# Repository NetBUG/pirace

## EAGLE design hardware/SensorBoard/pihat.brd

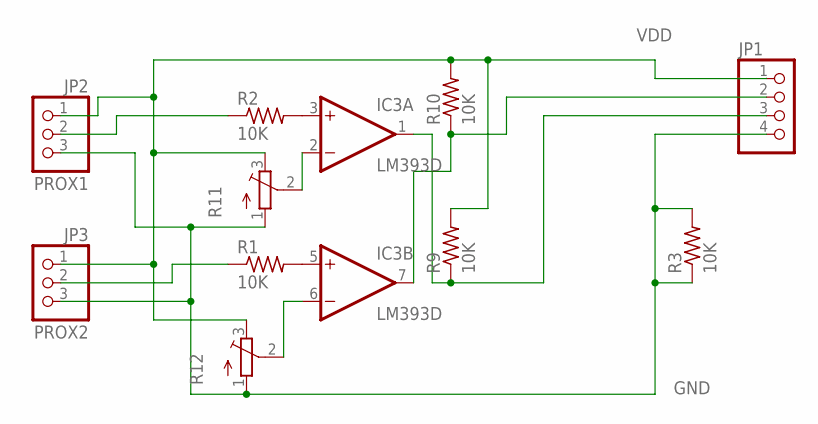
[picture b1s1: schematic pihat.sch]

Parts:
IC3: LM393D; SO08
JP1: PINHD-1X4; 1X04
JP2: PROX1; 1X03
JP3: PROX2; 1X03
R1, R2, R3, R9, R10: 10K; R1206FAB
R11, R12: TRIM_EU-3223G; 3223G

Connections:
GND: IC3.4 (V-), JP1.4, JP2.3, JP3.3, R3.1, R3.2, R11.1 (A), R12.1 (A)
unnamed: IC3.5 (+IN), R1.2
unnamed: IC3.3 (+IN), R2.2
unnamed: JP2.2, R2.1
unnamed: IC3.7 (OUT), JP1.2, R10.1
unnamed: IC3.1 (OUT), JP1.3, R9.1
unnamed: IC3.6 (-IN), R12.2 (S)
unnamed: IC3.2 (-IN), R11.2 (S)
unnamed: JP3.2, R1.1
VDD: IC3.8 (V+), JP1.1, JP2.1, JP3.1, R9.2, R10.2, R11.3 (E), R12.3 (E)

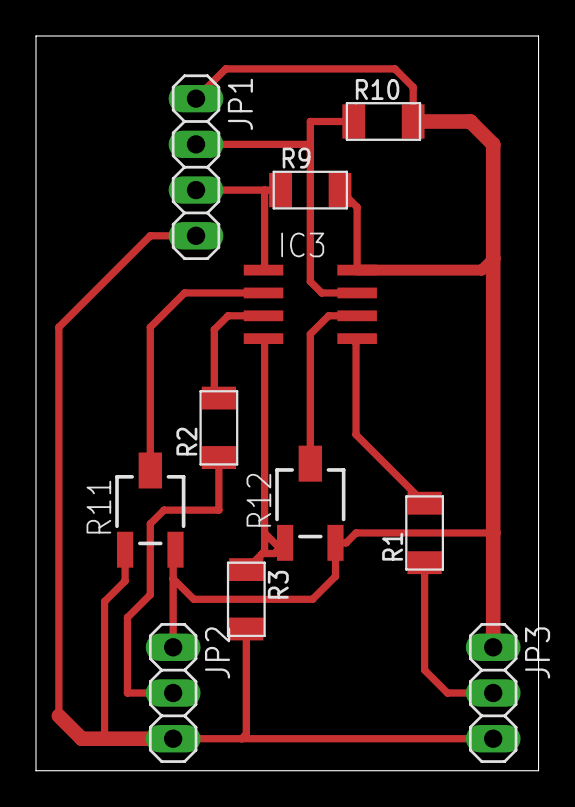
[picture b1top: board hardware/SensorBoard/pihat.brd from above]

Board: 2 copper layers, 27.9 x 40.8 mm, 11 parts (0 on the bottom side), 10 nets.

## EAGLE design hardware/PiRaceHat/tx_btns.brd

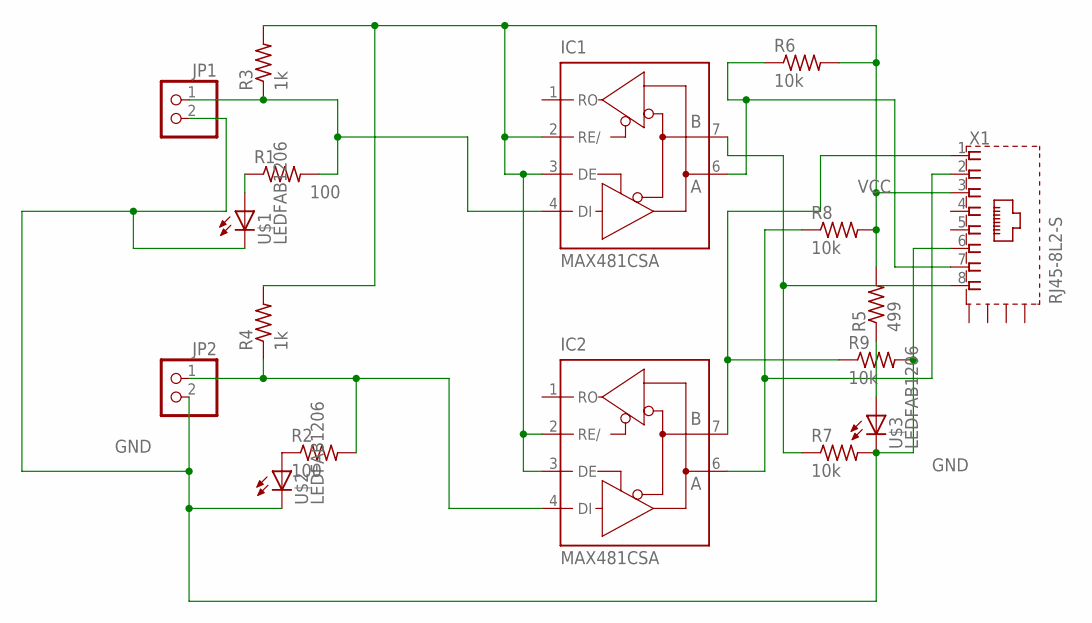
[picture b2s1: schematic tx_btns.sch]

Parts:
IC1, IC2: MAX481CSA; SO08
JP1, JP2: PINHD-1X2/90; 1X02/90
R1, R2: 100; R1206FAB
R3, R4: 1k; R1206FAB
R5: 499; R1206FAB
R6, R7, R8, R9: 10k; R1206FAB
U$1, U$2, U$3: LEDFAB1206; LED1206FAB
X1: RJ45-8L2-S; RJ45-SHIELD2

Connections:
GND: IC1.5 (GND), IC2.5 (GND), JP1.2, JP2.2, R7.2, R9.2, U$1.2 (C), U$2.2 (C), U$3.2 (C), X1.6
unnamed: R1.1, U$1.1 (A)
unnamed: R2.1, U$2.1 (A)
unnamed: R5.1, U$3.1 (A)
unnamed: IC1.4 (DI), JP1.1, R1.2, R3.1
unnamed: IC1.7 (B), R7.1, X1.8
unnamed: IC2.6 (A), R8.1, X1.2
unnamed: IC1.6 (A), R6.1, X1.7
unnamed: IC2.7 (B), R9.1, X1.1
unnamed: IC2.4 (DI), JP2.1, R2.2, R4.1
VCC: IC1.2 (RE/), IC1.3 (DE), IC1.8 (VCC), IC2.2 (RE/), IC2.3 (DE), IC2.8 (VCC), R3.2, R4.2, R5.2, R6.2, R8.2, X1.3

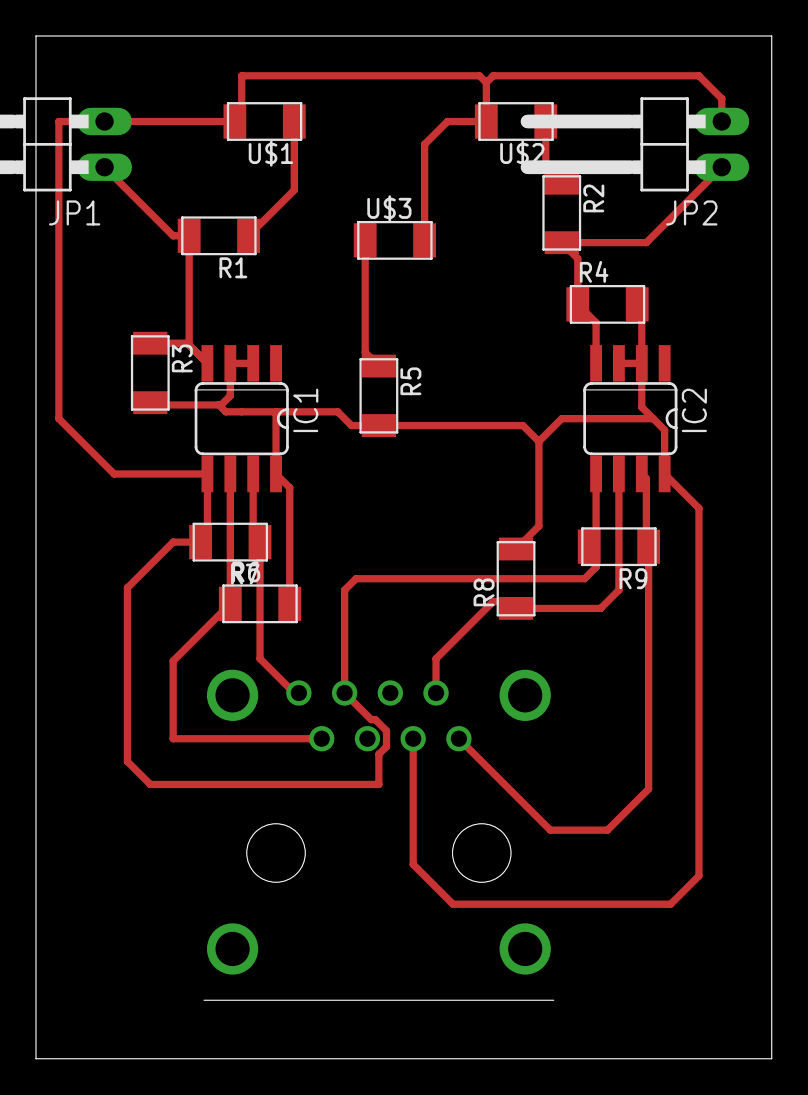
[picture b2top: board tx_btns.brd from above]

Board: 2 copper layers, 40.9 x 56.8 mm, 17 parts (1 on the bottom side), 11 nets.

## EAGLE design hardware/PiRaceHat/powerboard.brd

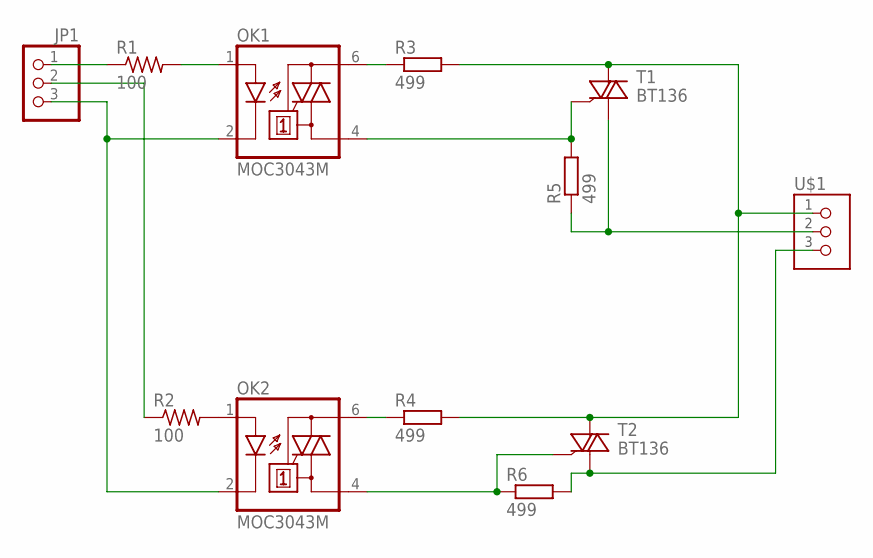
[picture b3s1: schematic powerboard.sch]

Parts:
JP1: PINHD-1X3/90; 1X03/90
OK1, OK2: MOC3043M; DIL06
R1, R2: 100; R1206FAB
R3, R4, R5, R6: 499; 0207/12
T1, T2: BT136; TO220AB
U$1: TERM-1X03'-FABLAB'; ED555DS-3DS

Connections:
unnamed: JP1.3, OK1.2 (C), OK2.2 (C)
unnamed: OK2.1 (A), R2.2
unnamed: JP1.2, R2.1
unnamed: OK1.1 (A), R1.2
unnamed: JP1.1, R1.1
unnamed: OK2.6 (A2), R4.1
unnamed: OK1.6 (A2), R3.1
unnamed: R3.2, R4.2, T1.2 (A2), T2.2 (A2), U$1.1
unnamed: R5.1, T1.1 (A1), U$1.2
unnamed: R6.2, T2.1 (A1), U$1.3
unnamed: OK1.4 (A1), R5.2, T1.3 (G)
unnamed: OK2.4 (A1), R6.1, T2.3 (G)

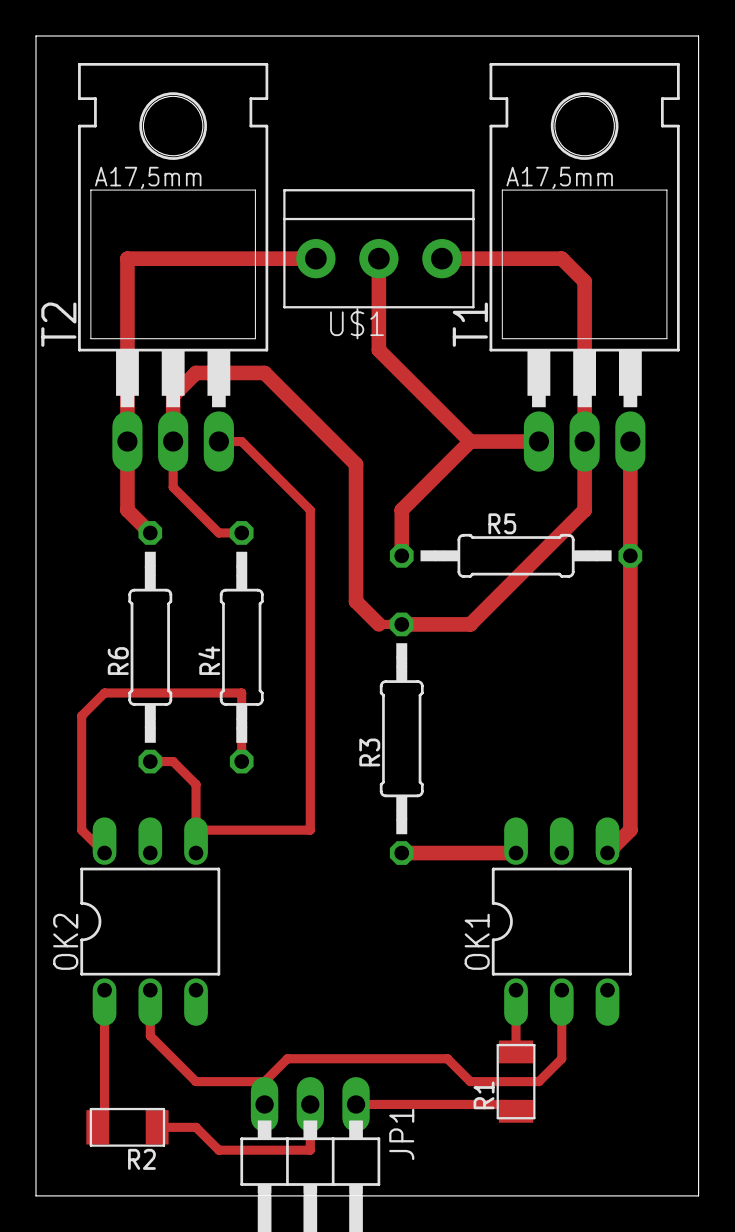
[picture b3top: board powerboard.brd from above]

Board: 2 copper layers, 36.8 x 64.4 mm, 12 parts (0 on the bottom side), 12 nets.

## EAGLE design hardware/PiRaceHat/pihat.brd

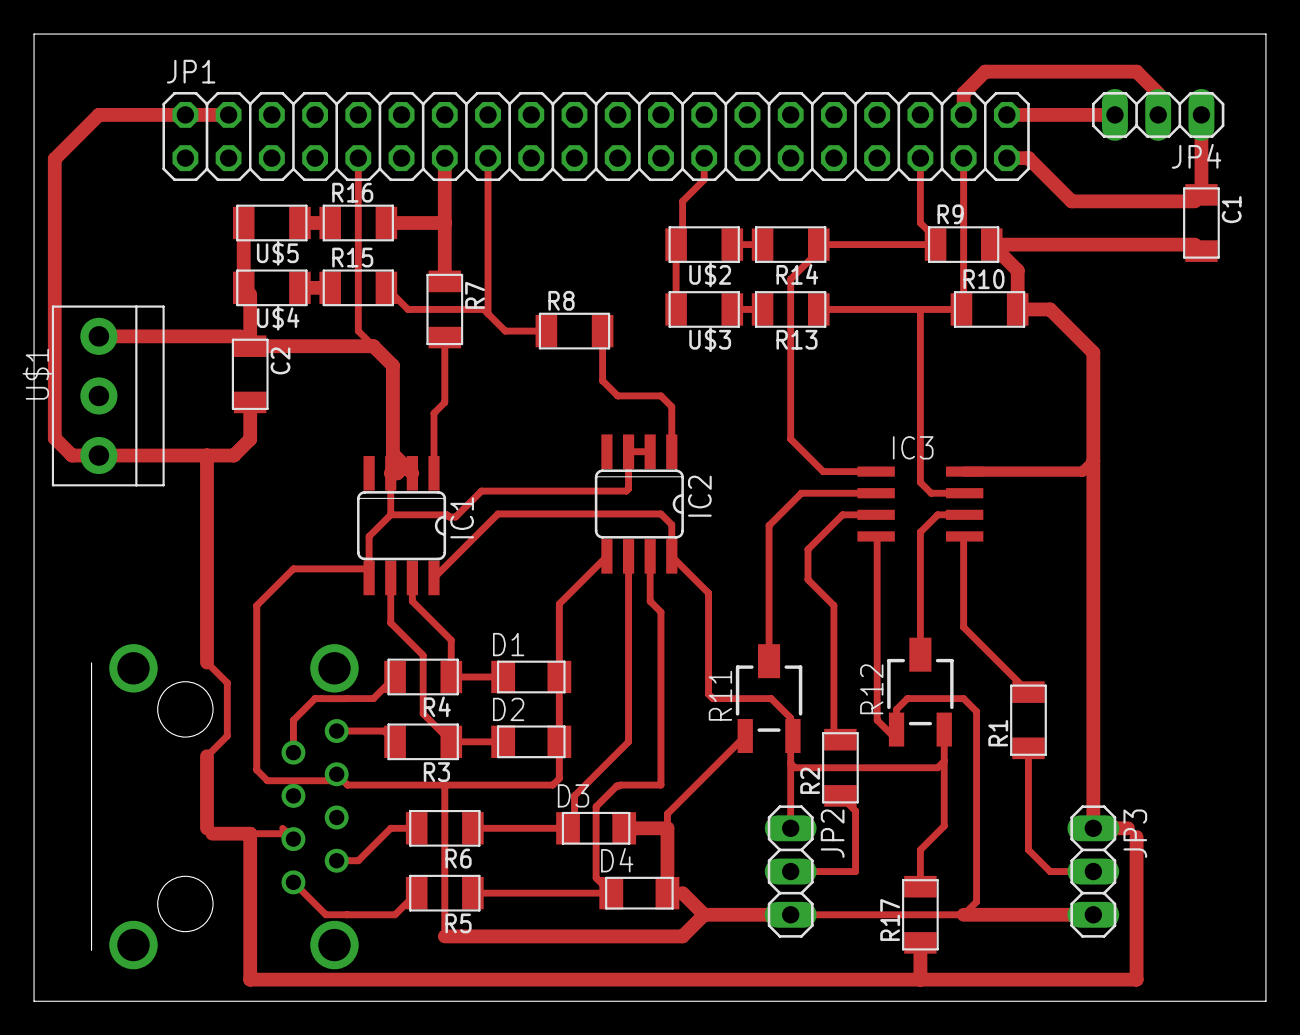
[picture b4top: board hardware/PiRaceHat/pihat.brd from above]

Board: 2 copper layers, 72.4 x 56.8 mm, 36 parts (1 on the bottom side), 28 nets.

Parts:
C1, C2: C1206FAB
D1, D2, D3, D4: CDBM1100-G; MINI-SMA
IC1, IC2: MAX481CSA; SO08
IC3: LM393D; SO08
JP1: 2X20
JP2: PROX1; 1X03
JP3: PROX2; 1X03
JP4: OUT; 1X03
R1, R2, R9, R10, R17: 10K; R1206FAB
R3, R4, R5, R6, R8: 49R; R1206FAB
R7: 49; R1206FAB
R11, R12: 3223G
R13, R14: 100R; R1206FAB
R15, R16: 100; R1206FAB
U$1: TERM-1X03'-FABLAB'; ED555DS-3DS
U$2, U$3, U$4, U$5: LEDFAB1206; LED1206FAB
X1: RJ45-6L21-B; RJ45-SHIELD1

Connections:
GND: C1.1, C2.1, D1.ANODE, D2.ANODE, D3.ANODE, D4.ANODE, IC1.2, IC1.3, IC1.5, IC2.2, IC2.3, IC2.5, IC3.4, JP1.6, JP1.9, JP1.14, JP1.20, JP1.25, JP1.30, JP1.34, JP1.39, JP2.3, JP3.3, JP4.1, R11.1, R12.1, U$1.3, U$2.2, U$3.2, U$4.2, U$5.2, X1.6
unnamed: IC3.5, R1.2
unnamed: IC3.3, R2.2
unnamed: D1.KATHODE, IC1.7, R4.1
unnamed: D2.KATHODE, IC1.6, R3.1
unnamed: R14.2, U$2.1
unnamed: D3.KATHODE, IC2.6, R6.1
unnamed: D4.KATHODE, IC2.7, R5.1
unnamed: JP2.2, R2.1
unnamed: R3.2, X1.8
unnamed: R4.2, X1.7
unnamed: R5.2, X1.1
unnamed: R6.2, X1.2
unnamed: R13.2, U$3.1
unnamed: IC1.1, R7.2
unnamed: IC2.1, R8.2
unnamed: JP1.13, R7.1, R16.2
unnamed: JP1.15, R8.1, R15.2
unnamed: IC3.7, JP1.37, R10.1, R13.1
unnamed: IC3.1, JP1.35, R9.1, R14.1
unnamed: IC3.6, R12.2
unnamed: IC3.2, R11.2
unnamed: R15.1, U$4.1
unnamed: JP3.2, R1.1
unnamed: R16.1, U$5.1
unnamed: JP1.40, JP4.3
unnamed: JP1.38, JP4.2
VDD: C1.2, C2.2, IC1.8, IC2.8, IC3.8, JP1.2, JP1.4, JP2.1, JP3.1, R9.2, R10.2, R11.3, R12.3, R17.1, U$1.1, X1.3

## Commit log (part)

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2019-07-28 Initial commit from Create React App
2019-07-28 First prototype
2019-07-28 Correct buttons operation
2019-07-28 Pass reset params to children
2019-07-28 Basic WS
2019-07-28 Add .gitignore for backend
2019-08-03 Make working server -- for tests
2019-08-03 Server backend
2019-08-05 Adapted GPIO bindings for buttons and sensors
2019-08-05 Backend for Pi and dev
2019-08-05 Updated stopwatch to handle bidirectinal communication correctly
2019-08-05 WOrking reset
2019-08-05 Proper design
2019-08-07 Remote control
2019-08-07 Unified entry point
2019-08-14 Avoid garbage files
2019-08-14 Adding hardware files: the case for optical finish line sensor
2019-08-14 Adding hardware files: Raspberry Pi hat with RS485 receivers and triggers
2019-08-14 Adding hardware files: Transmitter for buttons
2019-08-14 Stub for social network / cameras stuff
2019-08-14 Update run scripts
2019-08-14 Debugging_scripts
2019-08-18 Update startup scripts
2019-08-18 Add separate board with sensors (needed for connections over 1m to endstopds)
2019-09-06 Submit status to backend
2019-09-06 Fix button stop operations
2019-09-06 Fix race issues
2019-09-07 Experimental -- start timer instantly
2019-09-07 Erroneous timer @ startup
2019-09-07 Revert "Erroneous timer @ startup"
    This reverts commit 1f016ea12e93698ee3e5b621cf3487471f35d808.
2019-09-07 WORKING
2019-12-29 Bump handlebars from 4.1.2 to 4.5.3 in /webapp
    Bumps [handlebars](https://github.com/wycats/handlebars.js) from 4.1.2 to 4.5.3.
    - [Release notes](https://github.com/wycats/handlebars.js/releases)
    - [Changelog](https://github.com/wycats/handlebars.js/blob/master/release-notes.md)
    - [Commits](https://github.com/wycats/handlebars.js/compare/v4.1.2...v4.5.3)
2020-03-15 Bump acorn from 5.7.3 to 5.7.4 in /webapp
    Bumps [acorn](https://github.com/acornjs/acorn) from 5.7.3 to 5.7.4.
    - [Release notes](https://github.com/acornjs/acorn/releases)
    - [Commits](https://github.com/acornjs/acorn/compare/5.7.3...5.7.4)
2020-03-27 First release with NEDB
2020-03-27 Allowing mechanism
2020-07-17 Bump lodash from 4.17.15 to 4.17.19 in /webapp
    Bumps [lodash](https://github.com/lodash/lodash) from 4.17.15 to 4.17.19.
    - [Release notes](https://github.com/lodash/lodash/releases)
    - [Commits](https://github.com/lodash/lodash/compare/4.17.15...4.17.19)
2020-07-31 Bump elliptic from 6.5.0 to 6.5.3 in /webapp
    Bumps [elliptic](https://github.com/indutny/elliptic) from 6.5.0 to 6.5.3.
    - [Release notes](https://github.com/indutny/elliptic/releases)
    - [Commits](https://github.com/indutny/elliptic/compare/v6.5.0...v6.5.3)
2020-09-06 Bump handlebars from 4.1.2 to 4.7.6 in /webapp
    Bumps [handlebars](https://github.com/wycats/handlebars.js) from 4.1.2 to 4.7.6.
    - [Release notes](https://github.com/wycats/handlebars.js/releases)
    - [Changelog](https://github.com/handlebars-lang/handlebars.js/blob/master/release-notes.md)
    - [Commits](https://github.com/wycats/handlebars.js/compare/v4.1.2...v4.7.6)
2020-12-11 Bump ini from 1.3.5 to 1.3.7 in /srv
    Bumps [ini](https://github.com/isaacs/ini) from 1.3.5 to 1.3.7.
    - [Release notes](https://github.com/isaacs/ini/releases)
    - [Commits](https://github.com/isaacs/ini/compare/v1.3.5...v1.3.7)
2021-03-09 Bump elliptic from 6.5.0 to 6.5.4 in /webapp
    Bumps [elliptic](https://github.com/indutny/elliptic) from 6.5.0 to 6.5.4.
    - [Release notes](https://github.com/indutny/elliptic/releases)
    - [Commits](https://github.com/indutny/elliptic/compare/v6.5.0...v6.5.4)
2021-03-30 Bump y18n from 4.0.0 to 4.0.1 in /webapp
    Bumps [y18n](https://github.com/yargs/y18n) from 4.0.0 to 4.0.1.
    - [Release notes](https://github.com/yargs/y18n/releases)
    - [Changelog](https://github.com/yargs/y18n/blob/master/CHANGELOG.md)
    - [Commits](https://github.com/yargs/y18n/commits)
2021-04-30 Bump ssri from 6.0.1 to 6.0.2 in /webapp
    Bumps [ssri](https://github.com/npm/ssri) from 6.0.1 to 6.0.2.
    - [Release notes](https://github.com/npm/ssri/releases)
    - [Changelog](https://github.com/npm/ssri/blob/v6.0.2/CHANGELOG.md)
    - [Commits](https://github.com/npm/ssri/compare/v6.0.1...v6.0.2)
2021-05-08 Bump url-parse from 1.4.7 to 1.5.1 in /webapp
    Bumps [url-parse](https://github.com/unshiftio/url-parse) from 1.4.7 to 1.5.1.
    - [Release notes](https://github.com/unshiftio/url-parse/releases)
    - [Commits](https://github.com/unshiftio/url-parse/compare/1.4.7...1.5.1)
2021-05-10 Bump lodash from 4.17.15 to 4.17.21 in /webapp
    Bumps [lodash](https://github.com/lodash/lodash) from 4.17.15 to 4.17.21.
    - [Release notes](https://github.com/lodash/lodash/releases)
    - [Commits](https://github.com/lodash/lodash/compare/4.17.15...4.17.21)
2021-05-10 Bump hosted-git-info from 2.7.1 to 2.8.9 in /webapp
    Bumps [hosted-git-info](https://github.com/npm/hosted-git-info) from 2.7.1 to 2.8.9.
    - [Release notes](https://github.com/npm/hosted-git-info/releases)
    - [Changelog](https://github.com/npm/hosted-git-info/blob/v2.8.9/CHANGELOG.md)
    - [Commits](https://github.com/npm/hosted-git-info/compare/v2.7.1...v2.8.9)
2021-05-29 Bump ws from 7.1.1 to 7.4.6 in /srv
    Bumps [ws](https://github.com/websockets/ws) from 7.1.1 to 7.4.6.
    - [Release notes](https://github.com/websockets/ws/releases)
    - [Commits](https://github.com/websockets/ws/compare/7.1.1...7.4.6)
2021-06-08 Bump merge-deep from 3.0.2 to 3.0.3 in /webapp
    Bumps [merge-deep](https://github.com/jonschlinkert/merge-deep) from 3.0.2 to 3.0.3.
    - [Release notes](https://github.com/jonschlinkert/merge-deep/releases)
    - [Commits](https://github.com/jonschlinkert/merge-deep/compare/3.0.2...3.0.3)
    ---
    updated-dependencies:
    - dependency-name: merge-deep
2021-06-16 Bump postcss from 7.0.17 to 7.0.36 in /webapp
    Bumps [postcss](https://github.com/postcss/postcss) from 7.0.17 to 7.0.36.
    - [Release notes](https://github.com/postcss/postcss/releases)
    - [Changelog](https://github.com/postcss/postcss/blob/main/CHANGELOG.md)
    - [Commits](https://github.com/postcss/postcss/compare/7.0.17...7.0.36)
    ---
    updated-dependencies:
2021-09-21 Bump tmpl from 1.0.4 to 1.0.5 in /webapp
    Bumps [tmpl](https://github.com/daaku/nodejs-tmpl) from 1.0.4 to 1.0.5.
    - [Release notes](https://github.com/daaku/nodejs-tmpl/releases)
    - [Commits](https://github.com/daaku/nodejs-tmpl/commits/v1.0.5)
    ---
    updated-dependencies:
    - dependency-name: tmpl
2021-10-06 Bump url-parse from 1.4.7 to 1.5.3 in /webapp
    Bumps [url-parse](https://github.com/unshiftio/url-parse) from 1.4.7 to 1.5.3.
    - [Release notes](https://github.com/unshiftio/url-parse/releases)
    - [Commits](https://github.com/unshiftio/url-parse/compare/1.4.7...1.5.3)
    ---
    updated-dependencies:
    - dependency-name: url-parse
2022-01-13 Bump follow-redirects from 1.7.0 to 1.14.7 in /webapp
    Bumps [follow-redirects](https://github.com/follow-redirects/follow-redirects) from 1.7.0 to 1.14.7.
    - [Release notes](https://github.com/follow-redirects/follow-redirects/releases)
    - [Commits](https://github.com/follow-redirects/follow-redirects/compare/v1.7.0...v1.14.7)
    ---
    updated-dependencies:
    - dependency-name: follow-redirects
2022-02-10 Bump undefsafe from 2.0.2 to 2.0.5 in /srv
    Bumps [undefsafe](https://github.com/remy/undefsafe) from 2.0.2 to 2.0.5.
    - [Release notes](https://github.com/remy/undefsafe/releases)
    - [Commits](https://github.com/remy/undefsafe/compare/v2.0.2...v2.0.5)
    ---
    updated-dependencies:
    - dependency-name: undefsafe
2022-02-18 Bump url-parse from 1.4.7 to 1.5.7 in /webapp
    Bumps [url-parse](https://github.com/unshiftio/url-parse) from 1.4.7 to 1.5.7.
    - [Release notes](https://github.com/unshiftio/url-parse/releases)
    - [Commits](https://github.com/unshiftio/url-parse/compare/1.4.7...1.5.7)
    ---
    updated-dependencies:
    - dependency-name: url-parse
2022-02-26 Bump url-parse from 1.4.7 to 1.5.10 in /webapp
    Bumps [url-parse](https://github.com/unshiftio/url-parse) from 1.4.7 to 1.5.10.
    - [Release notes](https://github.com/unshiftio/url-parse/releases)
    - [Commits](https://github.com/unshiftio/url-parse/compare/1.4.7...1.5.10)
    ---
    updated-dependencies:
    - dependency-name: url-parse
2022-04-09 Bump moment from 2.24.0 to 2.29.2 in /srv
    Bumps [moment](https://github.com/moment/moment) from 2.24.0 to 2.29.2.
    - [Release notes](https://github.com/moment/moment/releases)
    - [Changelog](https://github.com/moment/moment/blob/develop/CHANGELOG.md)
    - [Commits](https://github.com/moment/moment/compare/2.24.0...2.29.2)
    ---
    updated-dependencies:
2022-07-07 Bump moment from 2.24.0 to 2.29.4 in /srv
    Bumps [moment](https://github.com/moment/moment) from 2.24.0 to 2.29.4.
    - [Release notes](https://github.com/moment/moment/releases)
    - [Changelog](https://github.com/moment/moment/blob/develop/CHANGELOG.md)
    - [Commits](https://github.com/moment/moment/compare/2.24.0...2.29.4)
    ---
    updated-dependencies:
2022-09-30 Bump @hapi/hoek and @hapi/joi in /webapp
    Bumps [@hapi/hoek](https://github.com/hapijs/hoek) and [@hapi/joi](https://github.com/hapijs/joi). These dependencies needed to be updated together.
    Updates `@hapi/hoek` from 6.2.4 to 8.5.1
    - [Release notes](https://github.com/hapijs/hoek/releases)
    - [Commits](https://github.com/hapijs/hoek/compare/v6.2.4...v8.5.1)
    Updates `@hapi/joi` from 15.1.0 to 15.1.1
    - [Release notes](https://github.com/hapijs/joi/releases)
2022-11-18 Bump loader-utils and react-scripts in /webapp
    Bumps [loader-utils](https://github.com/webpack/loader-utils) to 2.0.4 and updates ancestor dependency [react-scripts](https://github.com/facebook/create-react-app/tree/HEAD/packages/react-scripts). 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
    Updates `loader-utils` from 1.2.3 to 2.0.4
    - [Release notes](https://github.com/webpack/loader-utils/releases)
    - [Changelog](https://github.com/webpack/loader-utils/blob/v2.0.4/CHANGELOG.md)
    - [Commits](https://github.com/webpack/loader-utils/compare/v1.2.3...v2.0.4)
    Updates `react-scripts` from 3.0.1 to 5.0.1
2022-12-04 Bump decode-uri-component from 0.2.0 to 0.2.2 in /webapp
    Bumps [decode-uri-component](https://github.com/SamVerschueren/decode-uri-component) from 0.2.0 to 0.2.2.
    - [Release notes](https://github.com/SamVerschueren/decode-uri-component/releases)
    - [Commits](https://github.com/SamVerschueren/decode-uri-component/compare/v0.2.0...v0.2.2)
    ---
    updated-dependencies:
    - dependency-name: decode-uri-component
2022-12-09 Bump qs from 6.5.2 to 6.5.3 in /webapp
    Bumps [qs](https://github.com/ljharb/qs) from 6.5.2 to 6.5.3.
    - [Release notes](https://github.com/ljharb/qs/releases)
    - [Changelog](https://github.com/ljharb/qs/blob/main/CHANGELOG.md)
    - [Commits](https://github.com/ljharb/qs/compare/v6.5.2...v6.5.3)
    ---
    updated-dependencies:
2022-12-10 Bump express from 4.17.1 to 4.18.2 in /webapp
    Bumps [express](https://github.com/expressjs/express) from 4.17.1 to 4.18.2.
    - [Release notes](https://github.com/expressjs/express/releases)
    - [Changelog](https://github.com/expressjs/express/blob/master/History.md)
    - [Commits](https://github.com/expressjs/express/compare/4.17.1...4.18.2)
    ---
    updated-dependencies:
